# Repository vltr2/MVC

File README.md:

# MVC
An 8 bit computer project.  More details/work log at http://voltair.us/MVC.php

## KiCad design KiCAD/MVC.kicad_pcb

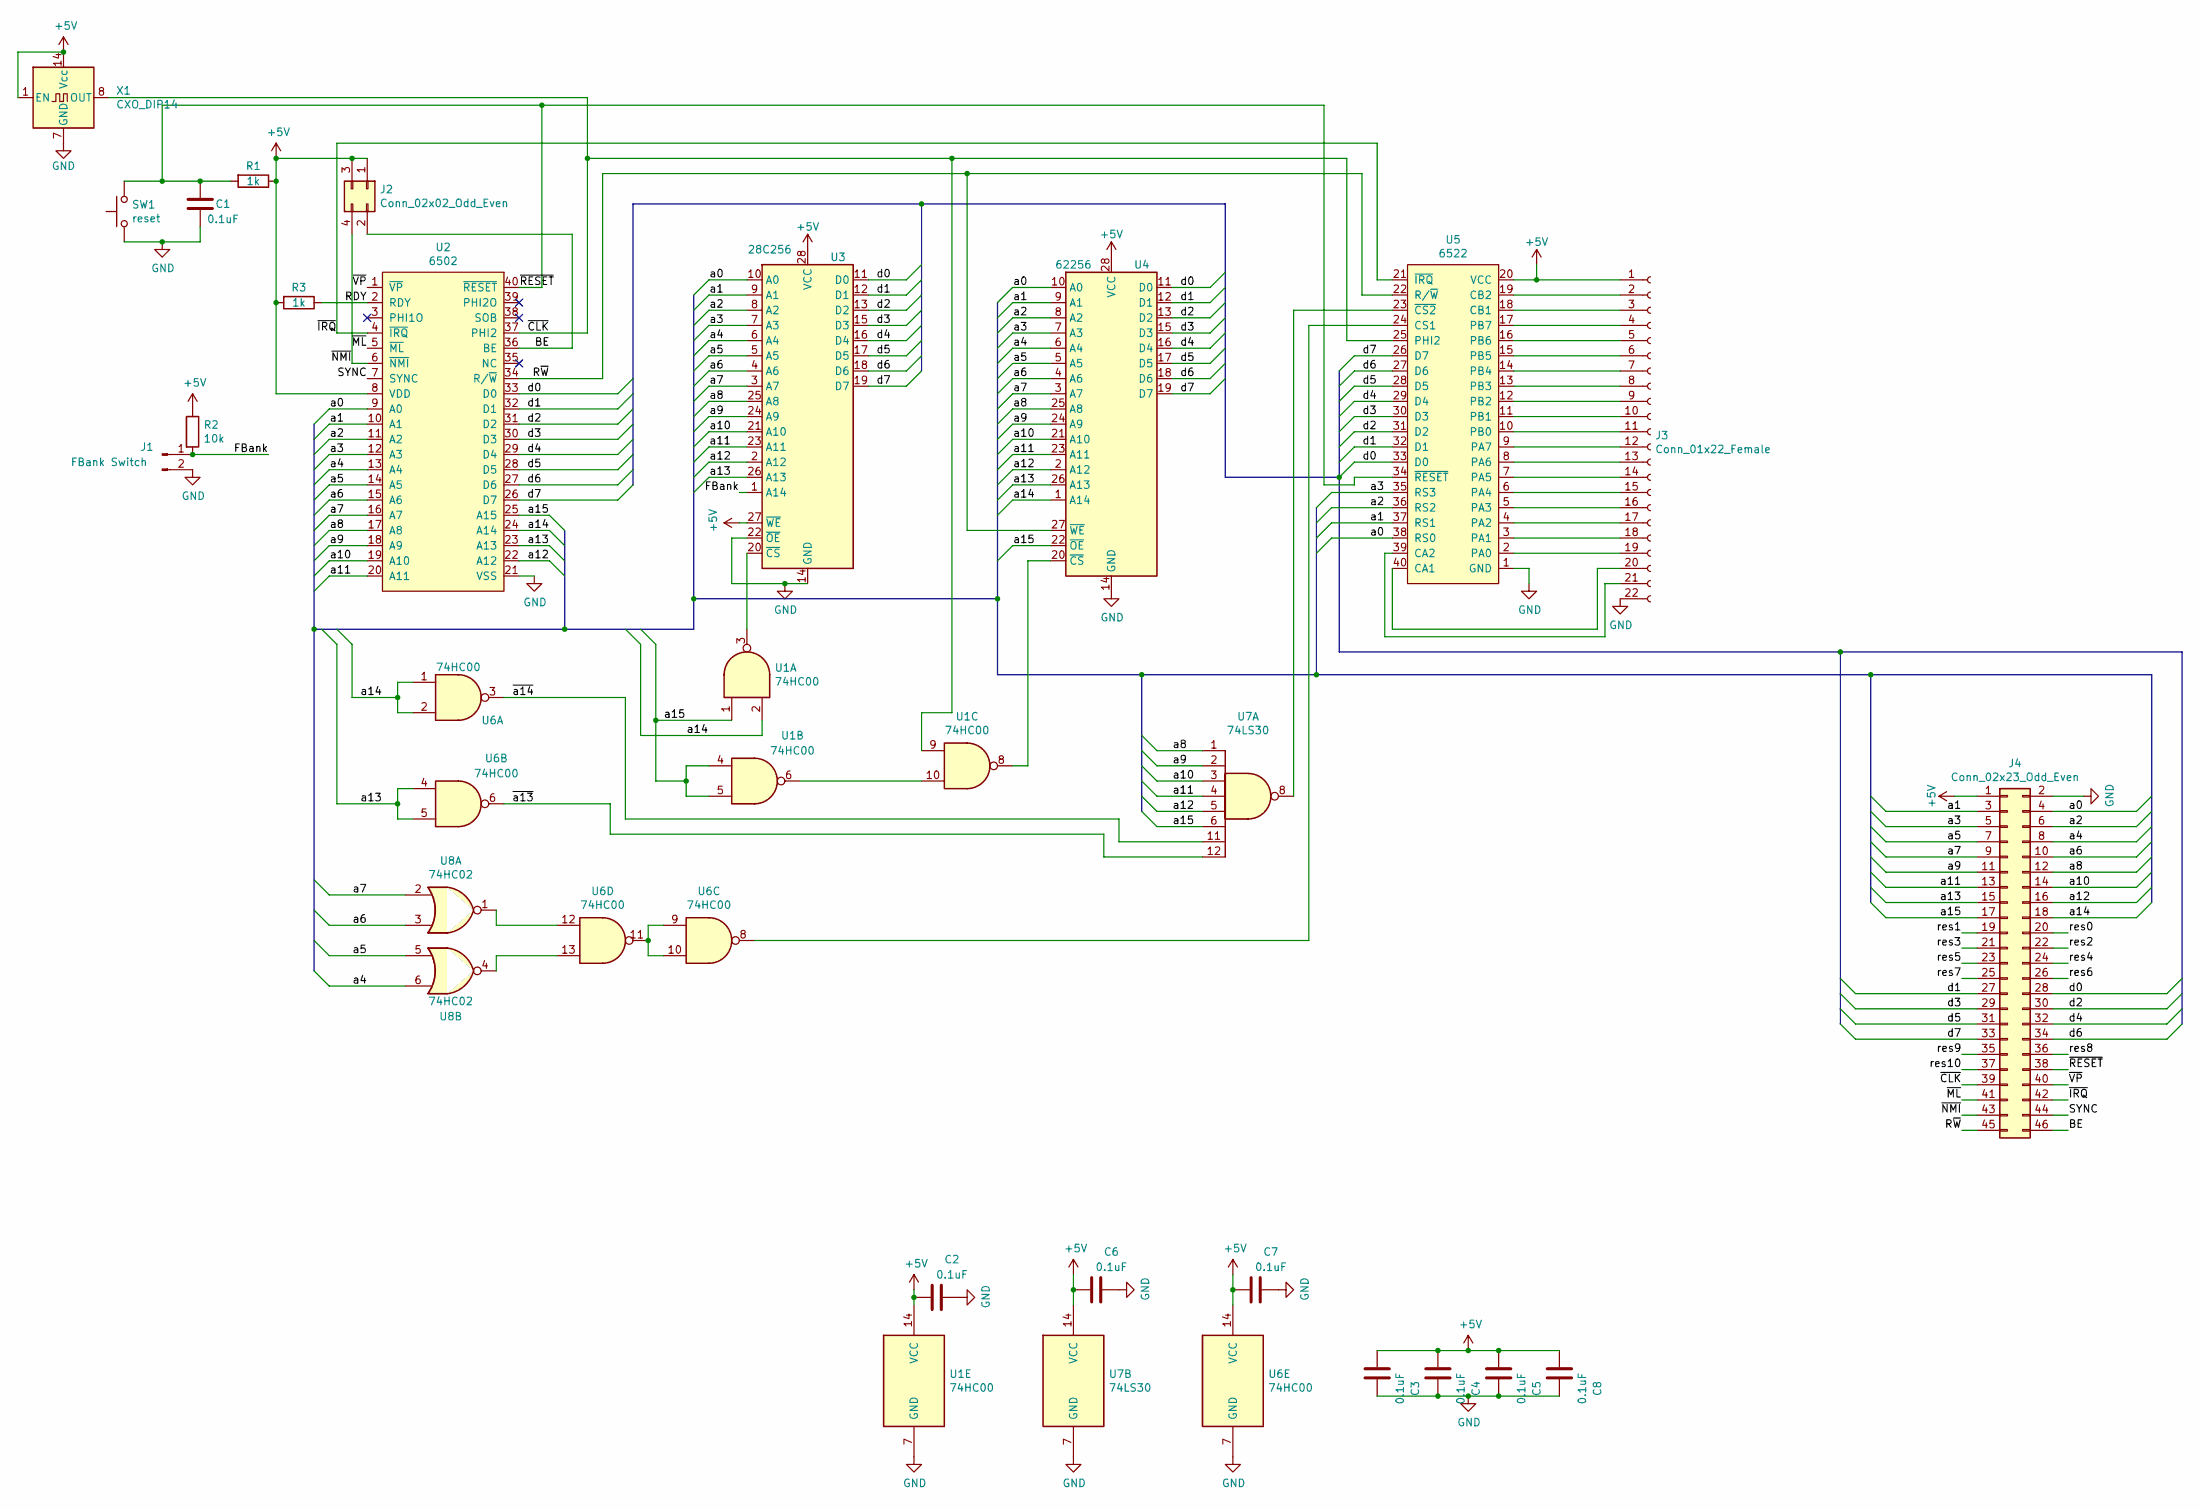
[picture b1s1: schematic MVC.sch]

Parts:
C1, C2, C3, C4, C5, C6, C7, C8: 0.1uF; CP_Radial_D5.0mm_P2.50mm
J1: FBank Switch; PinHeader_1x02_P2.54mm_Vertical
J2: Conn_02x02_Odd_Even; PinHeader_2x02_P2.54mm_Vertical
J3: Conn_01x22_Female; PinHeader_1x22_P2.54mm_Vertical
J4: Conn_02x23_Odd_Even; PinHeader_2x23_P2.54mm_Vertical
R1, R3: 1k; R_Axial_DIN0207_L6.3mm_D2.5mm_P7.62mm_Horizontal
R2: 10k; R_Axial_DIN0207_L6.3mm_D2.5mm_P7.62mm_Horizontal
SW1: reset; SW_PUSH_6mm
U1, U6: 74HC00; DIP-14_W7.62mm_Socket
U2: 6502; DIP-40_W15.24mm_Socket
U3: 28C256; DIP-28_W15.24mm_Socket
U4: 62256; DIP-28_W15.24mm_Socket
U5: 6522; DIP-40_W15.24mm_Socket
U7: 74LS30; DIP-14_W7.62mm_Socket
U8: 74HC02; DIP-14_W7.62mm_Socket
X1: CXO_DIP14; Oscillator_DIP-14

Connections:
+5V: C2.2, C3.2, C4.2, C5.2, C6.2, C7.2, C8.2, J2.1, J2.3, J3.1, J4.1, R1.1, R2.1, R3.2, U1.14 (VCC), U2.8 (VDD), U3.27 (~WE), U3.28 (VCC), U4.28 (VCC), U5.20 (VCC), U6.14 (VCC), U7.14 (VCC), X1.1 (EN), X1.14 (Vcc)
/BE: J2.2, J4.46, U2.36 (BE)
/FBank: J1.1, R2.2, U3.1 (A14)
/RDY: R3.1, U2.2 (RDY)
/R~W~: J4.45, U2.34 (R/~W~), U4.27 (~WE), U5.22 (R/~W~)
/SYNC: J4.44, U2.7 (SYNC)
/a0: J4.4, U2.9 (A0), U3.10 (A0), U4.10 (A0), U5.38 (RS0)
/a1: J4.3, U2.10 (A1), U3.9 (A1), U4.9 (A1), U5.37 (RS1)
/a2: J4.6, U2.11 (A2), U3.8 (A2), U4.8 (A2), U5.36 (RS2)
/a3: J4.5, U2.12 (A3), U3.7 (A3), U4.7 (A3), U5.35 (RS3)
/a4: J4.8, U2.13 (A4), U3.6 (A4), U4.6 (A4), U8.6
/a5: J4.7, U2.14 (A5), U3.5 (A5), U4.5 (A5), U8.5
/a6: J4.10, U2.15 (A6), U3.4 (A6), U4.4 (A6), U8.3
/a7: J4.9, U2.16 (A7), U3.3 (A7), U4.3 (A7), U8.2
/a8: J4.12, U2.17 (A8), U3.25 (A8), U4.25 (A8), U7.1
/a9: J4.11, U2.18 (A9), U3.24 (A9), U4.24 (A9), U7.2
/a10: J4.14, U2.19 (A10), U3.21 (A10), U4.21 (A10), U7.3
/a11: J4.13, U2.20 (A11), U3.23 (A11), U4.23 (A11), U7.4
/a12: J4.16, U2.22 (A12), U3.2 (A12), U4.2 (A12), U7.5
/a13: J4.15, U2.23 (A13), U3.26 (A13), U4.26 (A13), U6.4, U6.5
/a14: J4.18, U1.2, U2.24 (A14), U4.1 (A14), U6.1, U6.2
/a15: J4.17, U1.1, U1.4, U1.5, U2.25 (A15), U4.22 (~OE), U7.6
/d0: J4.28, U2.33 (D0), U3.11 (D0), U4.11 (D0), U5.33 (D0)
/d1: J4.27, U2.32 (D1), U3.12 (D1), U4.12 (D1), U5.32 (D1)
/d2: J4.30, U2.31 (D2), U3.13 (D2), U4.13 (D2), U5.31 (D2)
/d3: J4.29, U2.30 (D3), U3.15 (D3), U4.15 (D3), U5.30 (D3)
/d4: J4.32, U2.29 (D4), U3.16 (D4), U4.16 (D4), U5.29 (D4)
/d5: J4.31, U2.28 (D5), U3.17 (D5), U4.17 (D5), U5.28 (D5)
/d6: J4.34, U2.27 (D6), U3.18 (D6), U4.18 (D6), U5.27 (D6)
/d7: J4.33, U2.26 (D7), U3.19 (D7), U4.19 (D7), U5.26 (D7)
/res0: J4.20
/res1: J4.19
/res2: J4.22
/res3: J4.21
/res4: J4.24
/res5: J4.23
/res6: J4.26
/res7: J4.25
/res8: J4.36
/res9: J4.35
/res10: J4.37
/~CLK~: J4.39, U1.9, U2.37 (PHI2), U5.25 (PHI2), X1.8 (OUT)
/~IRQ~: J4.42, U2.4 (~IRQ~), U5.21 (~IRQ~)
/~ML~: J4.41, U2.5 (~ML~)
/~NMI~: J2.4, J4.43, U2.6 (~NMI~)
/~RESET~: C1.1, J4.38, R1.2, SW1.2, U2.40 (~RESET~), U5.34 (~RESET~)
/~VP~: J4.40, U2.1 (~VP~)
/~a13~: U6.6, U7.12
/~a14~: U6.3, U7.11
GND: C1.2, C2.1, C3.1, C4.1, C5.1, C6.1, C7.1, C8.1, J1.2, J3.22, J4.2, SW1.1, U1.7 (GND), U2.21 (VSS), U3.14 (GND), U3.22 (~OE), U4.14 (GND), U5.1 (GND), U6.7 (GND), U7.7 (GND), X1.7 (GND)
unnamed: J3.2, U5.19 (CB2)
unnamed: J3.3, U5.18 (CB1)
unnamed: J3.4, U5.17 (PB7)
unnamed: J3.5, U5.16 (PB6)
unnamed: J3.6, U5.15 (PB5)
unnamed: J3.7, U5.14 (PB4)
unnamed: J3.8, U5.13 (PB3)
unnamed: J3.9, U5.12 (PB2)
unnamed: J3.10, U5.11 (PB1)
unnamed: J3.11, U5.10 (PB0)
unnamed: J3.12, U5.9 (PA7)
unnamed: J3.13, U5.8 (PA6)
unnamed: J3.14, U5.7 (PA5)
unnamed: J3.15, U5.6 (PA4)
unnamed: J3.16, U5.5 (PA3)
unnamed: J3.17, U5.4 (PA2)
unnamed: J3.18, U5.3 (PA1)
unnamed: J3.19, U5.2 (PA0)
unnamed: J3.20, U5.40 (CA1)
unnamed: J3.21, U5.39 (CA2)
unnamed: U1.3, U3.20 (~CS)
unnamed: U1.8, U4.20 (~CS)
unnamed: U1.6, U1.10
unnamed: U5.23 (~CS2~), U7.8
unnamed: U5.24 (CS1), U6.8
unnamed: U6.9, U6.10, U6.11
unnamed: U6.12, U8.1
unnamed: U6.13, U8.4

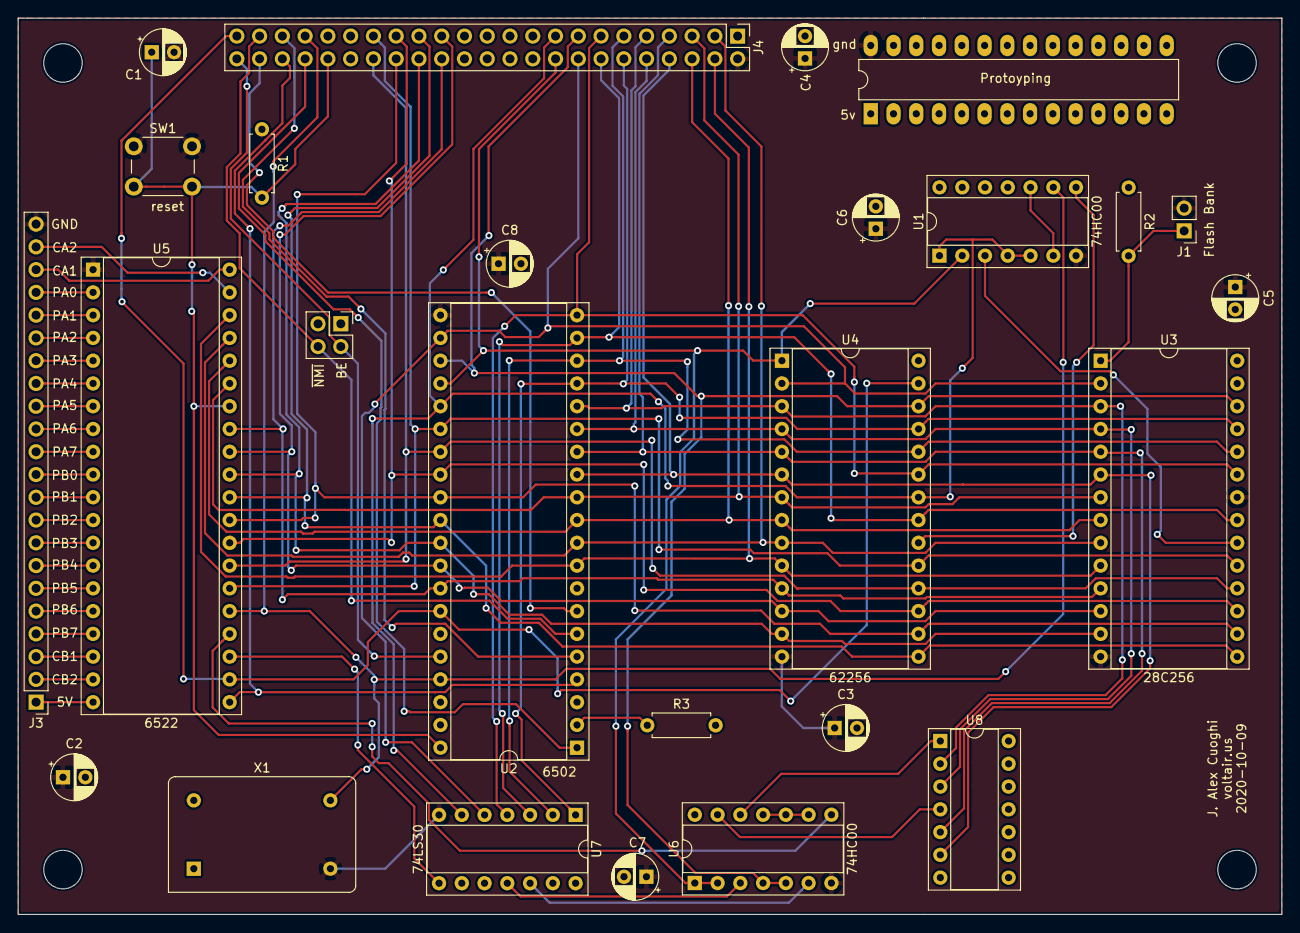
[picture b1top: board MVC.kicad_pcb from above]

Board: 2 copper layers, 141.0 x 100.0 mm, 25 parts (0 on the bottom side), 67 nets.

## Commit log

2020-09-12 Adding Arduino based monitor
2020-09-12 Added initial command capabilities
2020-09-13 Finished implementing current commands: clk,clr,run,spd
2020-09-13 Removed unused #include
2020-09-20 Adding Kicad project files for initial schematic work
2020-09-20 Working on schematic
2020-09-23 Delete .gitignore
    fixing pull issues
2020-09-23 Delete extensions.json
    fixing pull issues
2020-09-24 Added tic - single step command
2020-09-29 Working on basic schematic
2020-10-01 Finshed ugly schematic start on PCB
2020-10-09 Built first ugly mainboard
2020-11-08 Added Hello World code for basic testing
2021-01-23 Added note on lcd_wait vs lcd_busy
2021-02-07 Fixed incorect jsr lcd_busy to lcd_wait
2021-02-07 Completed Hello_World.s to print out full message for hardware test.
2021-05-02 Fixed issues found in PCB over testing through apr
2021-05-05 Begun moving addresses to seperate file as test
2021-05-05 Actually added Helloworld + readme cleanup
2021-05-09 Added KiCAD project for serial board addon
2021-05-10 Built Schematic for Serial Addon Board
2021-06-18 Created PCB for serial add on board
